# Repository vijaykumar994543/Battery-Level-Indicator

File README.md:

# Battery Level Indicator using KiCad

## Description
This project implements a battery level indicator circuit and PCB design using KiCad.

## Working
1. The circuit is designed to indicate the battery level.
2. The schematic shows the electrical connections between components.
3. The PCB layout shows component placement and copper routing.
4. The 3D model provides a visual representation of the PCB.

## Tools Used
- KiCad
- KiCad Schematic Editor
- KiCad PCB Editor
- KiCad 3D Viewer

## Files
- `batterylevelindicator.kicad_sch` : Schematic design
- `batterylevelindicator.kicad_pcb` : PCB design
- `schematic.png` : Schematic image
- `pcb.png` : PCB layout image
- `3D Model.png` : 3D PCB model

## Schematic

## PCB Layout

## 3D Model

## Result
The battery level indicator schematic and PCB layout were designed using KiCad. The 3D model helps visualize the board before manufacturing.

## Author
Vijay Kumar

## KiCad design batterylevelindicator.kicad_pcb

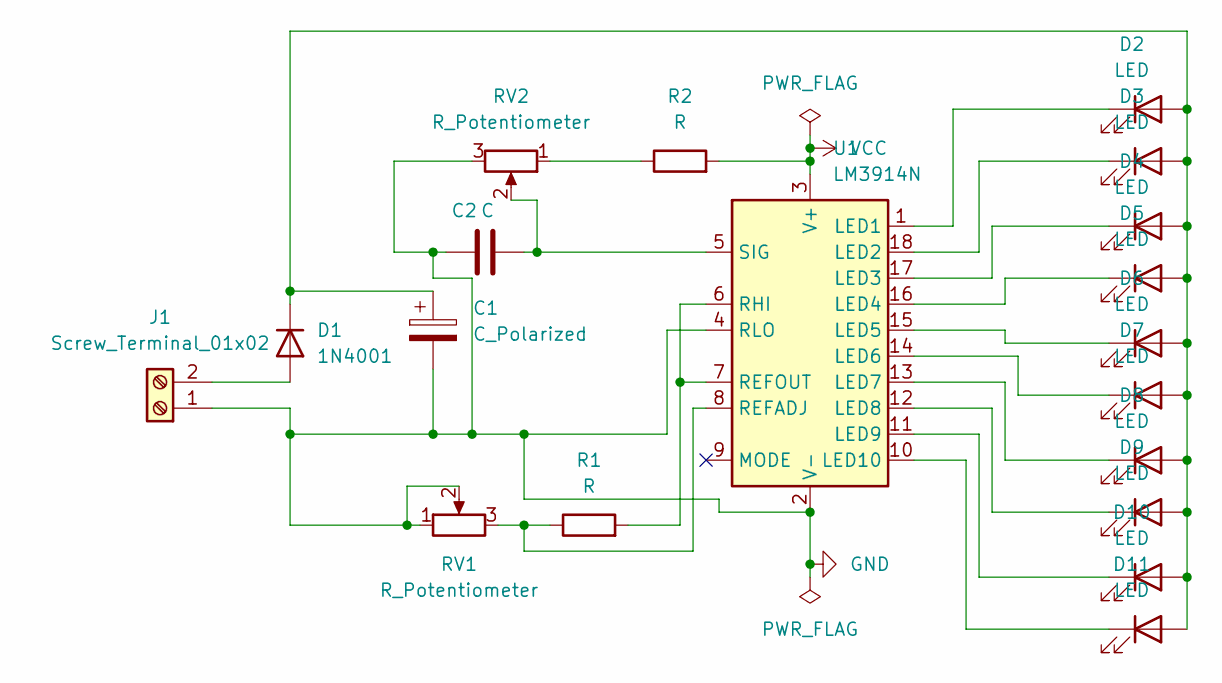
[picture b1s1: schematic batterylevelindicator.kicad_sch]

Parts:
C1: C_Polarized; CP_Radial_D6.3mm_P2.50mm
C2: C; C_Disc_D3.8mm_W2.6mm_P2.50mm
D1: 1N4001; D_DO-41_SOD81_P10.16mm_Horizontal
D2, D3, D4, D5, D6, D7, D8, D9, D10, D11: LED; LED_D3.0mm
J1: Screw_Terminal_01x02; TerminalBlock_Phoenix_MKDS-1,5-2-5.08_1x02_P5.08mm_Horizont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
R1, R2: R; R_Axial_DIN0207_L6.3mm_D2.5mm_P10.16mm_Horizontal
RV1, RV2: R_Potentiometer; Potentiometer_Bourns_3296W_Vertical
U1: LM3914N; DIP-18_W7.62mm

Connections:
GND: C1.2, C2.1, J1.1, RV1.1, RV1.2, RV2.3, U1.2 (V-), U1.4 (RLO)
unnamed: D1.2 (A), J1.2
unnamed: C1.1, D1.1 (K), D2.2 (A), D3.2 (A), D4.2 (A), D5.2 (A), D6.2 (A), D7.2 (A), D8.2 (A), D9.2 (A), D10.2 (A), D11.2 (A)
unnamed: D2.1 (K), U1.1 (LED1)
unnamed: D3.1 (K), U1.18 (LED2)
unnamed: D4.1 (K), U1.17 (LED3)
unnamed: D5.1 (K), U1.16 (LED4)
unnamed: D6.1 (K), U1.15 (LED5)
unnamed: D7.1 (K), U1.14 (LED6)
unnamed: D8.1 (K), U1.13 (LED7)
unnamed: D9.1 (K), U1.12 (LED8)
unnamed: D10.1 (K), U1.11 (LED9)
unnamed: D11.1 (K), U1.10 (LED10)
unnamed: R2.1, RV2.1
unnamed: R1.1, RV1.3, U1.8 (REFADJ)
unnamed: R1.2, U1.6 (RHI), U1.7 (REFOUT)
unnamed: C2.2, RV2.2, U1.5 (SIG)
VCC: R2.2, U1.3 (V+)

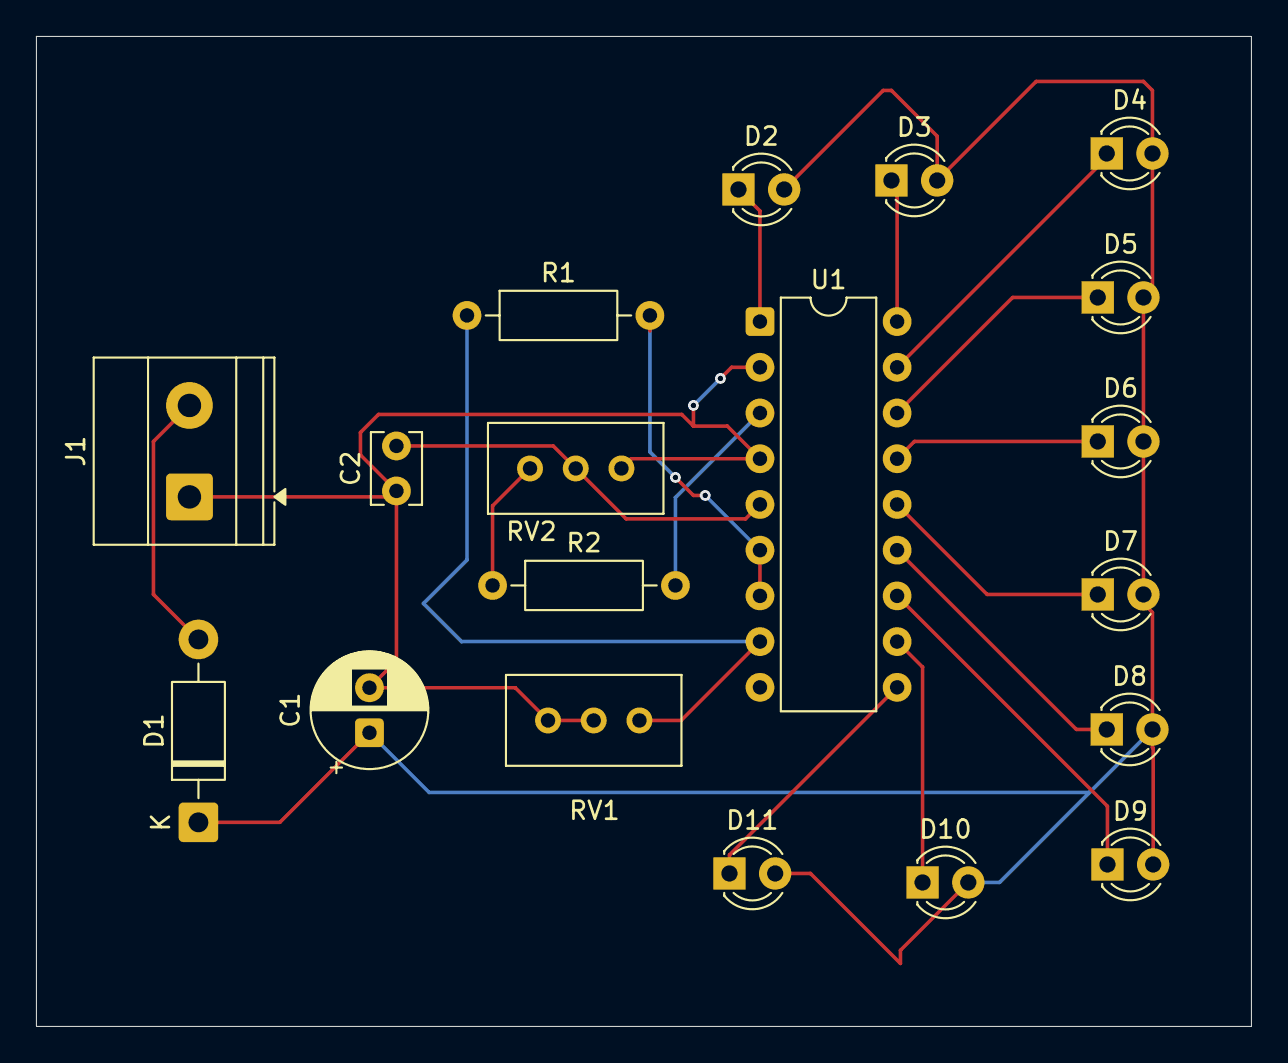
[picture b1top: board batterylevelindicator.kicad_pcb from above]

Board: 2 copper layers, 67.5 x 55.0 mm, 19 parts (0 on the bottom side), 18 nets.
